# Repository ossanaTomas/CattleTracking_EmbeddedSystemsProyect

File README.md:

# Cattle Tracking System — Embedded Systems Project

## Table of Contents

- [Motivation](#motivation)
- [Overview](#overview)
- [Key Features](#key-features)
- [Repository Structure](#repository-structure)
- [Hardware Design](#hardware-design)
  - [Tracker Board (Collar Node)](#tracker-board-collar-node)
  - [Base Station Board](#base-station-board)
- [Firmware](#firmware)
  - [Tracker Firmware](#tracker-firmware-firmwarefirmware-tracker)
  - [Base Station Firmware](#base-station-firmware-firmwarefirmware-base-station)
- [Communication Protocol](#communication-protocol)
- [Dashboard Application](#dashboard-application-dashboard-app)
- [Technology Stack Summary](#technology-stack-summary)
- [Academic Context](#academic-context)
- [Author](#author)

---

## Motivation

My father is a farmer. Every single day he drives out to the field to walk the land, check on the animals, make sure they are healthy and in the right paddock. It is a time-consuming routine that depends entirely on being physically present.

That got me thinking: what if I could apply my knowledge as an engineering student to make his daily work easier? With a satellite tracking system he could simply pull out his phone, check an app, and know the status of every animal in real time — without leaving the house.

That question became this project. For the *Programación de Sistemas Embebidos* course I decided to build a **low-power, long-range embedded solution** that tackles exactly that problem. The result is a working prototype: custom PCBs, bare-metal firmware, a LoRa radio link, and a web dashboard, all built from scratch.

The system is still a prototype and has room to grow in several areas, but it is **fully functional** — and with a reasonable amount of additional development it could be deployed in a real field environment without any fundamental obstacles.

---

## Overview

An end-to-end **IoT solution for GPS-based livestock tracking** built entirely from scratch — custom PCBs, embedded firmware, and a web dashboard included.

The goal was to design a **low-power, long-range** monitoring system that can be attached to cattle collars. Each collar (tracker node) periodically collects GPS coordinates and body temperature, and transmits this data wirelessly to a fixed base station using **LoRa radio modules**. The base station forwards all received data to a PC, where a web application stores and visualizes it in real time.

```
┌─────────────────────────────────────────────────────────────────┐
│                         FIELD                                   │
│                                                                 │
│  ┌──────────────┐       LoRa        ┌──────────────────────┐   │
│  │   Tracker    │ ────────────────► │    Base Station      │   │
│  │  (Collar)    │ ◄──────── ACK/CFG │  (Fixed / Fencepost) │   │
│  │              │                   │                      │   │
│  │ STM32F103    │                   │ STM32F103            │   │
│  │ GPS (u-blox) │                   │ USB CDC              │   │
│  │ DS18B20 Temp │                   └──────────┬───────────┘   │
│  │ SX127x LoRa  │                              │               │
│  └──────────────┘                              │ USB Serial    │
│                                                │               │
└────────────────────────────────────────────────┼───────────────┘
                                                 │
                                    ┌────────────▼──────────────┐
                                    │     Dashboard App (PC)    │
                                    │   FastAPI + SQLite + Web  │
                                    └───────────────────────────┘
```

---

## Key Features

- **GPS tracking** — latitude, longitude, satellite count and heading, with 0.0001° precision
- **Temperature monitoring** — DS18B20 sensor with 0.001 °C resolution
- **Battery voltage monitoring** — reported in millivolts
- **LoRa radio link** — long-range, low-power wireless communication (SX127x modules)
- **Two operating modes** — Continuous (every 30 s) and Low-Power (configurable interval with GPS pre-warming)
- **Reliable delivery (Stop-and-Wait ARQ)** — every DATA frame is acknowledged; unacknowledged frames are retried
- **Remote reconfiguration** — the base station can push configuration changes (mode, interval, GPS timers) via piggybacked ACK frames
- **Persistent configuration** — node settings survive power cycles (stored in Flash)
- **CRC16-CCITT integrity checks** — every frame is verified on both ends
- **Comprehensive error reporting** — 16-bit error mask covers GPS fix failures, sensor errors, battery alerts, and radio issues
- **Web dashboard** — real-time visualization of all received telemetry; debug view with raw frame inspection

---

## Repository Structure

```
EmbeddedSystemProyect/
├── firmware/
│   ├── firmware-tracker/          # STM32 firmware for the collar node
│   │   ├── Core/
│   │   │   ├── Inc/               # Header files
│   │   │   └── Src/               # C source files
│   │   ├── Drivers/               # STM32 HAL + CMSIS
│   │   └── EmbeddedSystemProyect.ioc
│   └── firmware-base-station/     # STM32 firmware for the base station
│       ├── Core/
│       │   ├── Inc/
│       │   └── Src/
│       ├── Drivers/
│       ├── Middlewares/           # USB Device stack (CDC)
│       └── Base_station.ioc
├── hardware/
│   ├── kicad/
│   │   ├── tracker-board/         # KiCad schematic + PCB for the collar
│   │   └── base-station-board/    # KiCad schematic + PCB for the base station
│   └── images/
│       ├── tracker-boad/          # Schematics, renders, and photos — tracker
│       └── base-station-board/    # Schematics, renders, and photos — base station
└── dashboard-app/                 # Python FastAPI web application
    ├── app/
    │   ├── api/                   # REST endpoints
    │   ├── db/                    # SQLAlchemy models + SQLite session
    │   ├── proto/                 # Frame parser + CRC16
    │   ├── serial/                # Serial port reader (USB CDC)
    │   └── web/                   # Jinja2 templates (dashboard, debug, mode)
    └── requirements.txt
```

---

## Hardware Design

Both boards were designed from scratch in **KiCad**, manufactured, hand-assembled, and tested.

### Tracker Board (Collar Node)

The tracker is a compact, battery-powered board designed to be mounted on a livestock collar. It integrates the microcontroller, LoRa module footprint, GPS connector, temperature sensor interface, and power management in a single PCB.

**Schematic**

**PCB Layout**

**3D Renders**

| Front | Back |
|-------|------|
|  |  |

**Fabrication & Assembly**

**Mounted on Collar**

---

### Base Station Board

The base station is a fixed-installation board. It receives LoRa frames from all trackers in range and forwards the raw data to a PC over USB (CDC virtual serial port).

**Schematic**

**PCB Layout**

**3D Renders**

**Fabrication & Result**

---

## Firmware

Both firmware projects target the **STM32F103C8T6** (ARM Cortex-M3, 64 KB Flash, 20 KB RAM) and were developed using **STM32CubeIDE**. 

### Tracker Firmware (`firmware/firmware-tracker`)

The tracker firmware follows a clean layered architecture:

```
┌─────────────────────────────────────────┐
│          Application Layer              │  node.c — NodeSimple_Task()
│  (mode management, data collection,     │  node_cfg.c — Flash persistence
│   TX scheduling, RX window)             │
├─────────────────────────────────────────┤
│           Service Layer                 │  gps.c — NMEA / UBX parser
│  (sensor acquisition, GPS management,  │  service_temp.c — DS18B20 service
│   temperature, battery)                 │
├─────────────────────────────────────────┤
│          Protocol Layer                 │  frame.c — pack/unpack frames
│  (framing, CRC16, ARQ link layer)       │  crc16_ccitt.c
│                                         │  node_link.c — Stop-and-Wait ARQ
├─────────────────────────────────────────┤
│       Hardware Abstraction Layer        │  LoRa.c — SX127x SPI driver
│  (LoRa radio, OneWire, UART, SPI, GPIO) │  ds18b20.c + onewire_uart.c
│                                         │  STM32 HAL (SPI1, USART1/2, GPIO)
└─────────────────────────────────────────┘
```

#### Peripheral Mapping

| Peripheral | Pins | Purpose |
|-----------|------|---------|
| SPI1 | PA5 / PA6 / PA7 | LoRa SX127x data bus (SCK / MISO / MOSI) |
| GPIO | PB0 / PB1 / PB10 | LoRa NSS (chip-select) / RST / DIO0 (IRQ) |
| USART1 | PA9 / PA10 | GPS UART @ 9600 baud (NMEA + UBX) |
| GPIO | PB11 | GPS power enable |
| USART2 | PA2 (half-duplex) | OneWire bus for DS18B20 @ 115200 baud |
| GPIO | PC13 | Status LED |
| SWD | PA13 / PA14 | Programming interface |

#### Operating Modes

**Continuous Mode (`NODE_MODE_CONTINUOUS`)**
Transmits a DATA frame every 30 seconds with the GPS running continuously. Prioritizes update frequency over power consumption — suitable for short-duration operations or testing.

**Low-Power Mode (`NODE_MODE_LOW_POWER`)**
Designed for multi-day battery life. The GPS is kept off between transmissions. Before each scheduled TX, the GPS is powered on for a configurable pre-warm period (`gps_prewarm_s`) to start acquiring satellites. An additional wait (`gps_extra_wait_s`) is allowed to obtain a valid fix. After transmission, the GPS is powered down again.

Both modes and their timing parameters are configurable and persist across reboots in **Flash memory** (last 1 KB page at address `0x0800F800`).

#### Reliable Delivery (Stop-and-Wait ARQ)

After each DATA frame is transmitted, the node opens a **receive window** waiting for an ACK from the base station. If no ACK is received within the timeout, the frame is retried up to `n_retries` times. The ACK frame can optionally carry a `CFG` payload, allowing the base station to push updated configuration to the node without a separate control channel.

#### Initialization Sequence

```
HAL_Init() → SystemClock_Config()
  → MX_GPIO_Init()
  → MX_USART1_UART_Init()  (GPS @ 9600 baud)
  → MX_USART2_UART_Init()  (OneWire / DS18B20 @ 115200 baud)
  → MX_SPI1_Init()         (LoRa @ 8 Mbit/s)
  → GPS_Init()
  → TempService_Init(&huart2, DS18B20_RES_10BIT)
  → LoRa_init()            (retried up to 50 times)
  → NodeSimple_Init(lora, node_id=1, net_id=0x27)
  → while(1) NodeSimple_Task()
```

---

### Base Station Firmware (`firmware/firmware-base-station`)

The base station is simpler by design. Its responsibilities are:

1. Continuously listen on the LoRa channel for incoming DATA frames
2. Send an ACK frame back to the transmitting node (optionally with a CFG payload)
3. Forward received frames to the PC over **USB CDC** (virtual serial port)
4. Accept commands from the PC (`pc_cmd.c`) to push configuration changes to specific nodes

It exposes a USB CDC virtual COM port to the host PC, over which raw received frames (prefixed with RSSI) are streamed. The dashboard app reads this serial stream.

---

## Communication Protocol

All LoRa transmissions use a custom binary framing protocol with CRC integrity verification.

### Frame Structure

```
 ┌──────────────────────────┬────────────────────┬───────────────┐
 │       HEADER (8 bytes)   │  PAYLOAD (variable) │  CRC16 (2 B)  │
 └──────────────────────────┴────────────────────┴───────────────┘

Header fields:
  [0] VER    — Protocol version (0x01)
  [1] NET    — Network ID (0x27 by default)
  [2] TYPE   — Message type
  [3] SRC    — Source node address
  [4] DST    — Destination address (0xFF = broadcast)
  [5] SEQ    — Sequence number (0–255, wraps around)
  [6] FLAGS  — Validity bits (GPS_VALID | TEMP_VALID | BATT_VALID)
  [7] PLEN   — Payload length in bytes
```

### Message Types

| Type | Code | Direction | Description |
|------|------|-----------|-------------|
| DATA | `0x10` | Tracker → Base | Sensor telemetry payload |
| ERR  | `0x11` | Tracker → Base | Error notification with text |
| ACK  | `0x30` | Base → Tracker | Acknowledgment (may carry CFG) |
| CFG  | `0x20` | Base → Tracker | Remote configuration update |

### DATA Payload (27 bytes)

```c
typedef struct {
    uint32_t t_ms;            // Node uptime in milliseconds
    uint32_t utc_raw_x1e3;    // UTC time from GPS (x1000)
    int32_t  lat_raw_x1e4;    // Latitude  ddmm.mmmm x 10000 (negative = S)
    int32_t  lon_raw_x1e4;    // Longitude dddmm.mmmm x 10000 (negative = W)
    uint8_t  sats;            // Number of satellites in view
    uint16_t course_cdeg;     // Heading in centidegrees (degrees x 100)
    int32_t  temp_mC;         // Temperature in milli-Celsius
    uint16_t batt_mV;         // Battery voltage in millivolts
    uint16_t err_mask;        // 16-bit error flags
} proto_data_t;
```

### Error Mask Bits

| Bit | Meaning |
|-----|---------|
| 0 | GPS no fix |
| 1 | GPS parse error |
| 2 | GPS configuration error |
| 3 | Temperature sensor read failure |
| 4 | Temperature sensor not detected |
| 5 | Battery voltage critical |
| 6 | LoRa TX failure |
| 7 | ACK timeout (max retries exceeded) |
| 8 | CRC verification failure |

### CFG Payload (6 bytes)

The base station can remotely reconfigure any tracker by piggybacking a CFG payload onto the ACK response:

```c
typedef struct {
    uint8_t  cfg_seq;        // Sequence number (idempotent updates)
    uint8_t  mode;           // 0 = CONTINUOUS, 1 = LOW_POWER
    uint16_t interval_s;     // TX interval in seconds (Low-Power mode)
    uint8_t  gps_prewarm_s;  // Seconds to power GPS before TX
    uint8_t  gps_extra_s;    // Extra seconds to wait for GPS fix
} proto_cfg_t;
```

---

## Dashboard Application (`dashboard-app`)

A Python web application that receives telemetry from the base station and exposes it through a browser-based interface.

### Architecture

```
USB Serial (base station)
        │
        ▼
  SerialManager        ← background thread, reads raw frames
        │
        ▼
  Frame Parser         ← unpack header + payload, verify CRC16
        │
        ▼
  SQLite Database      ← stores Node and Frame records (SQLAlchemy)
        │
        ├──► REST API  (/api/...)   ← JSON endpoints
        └──► Web UI    (/dashboard, /debug, /mode)
```

### Components

| Module | Role |
|--------|------|
| `serial/serial_manager.py` | Reads raw bytes from USB CDC serial port in a background thread |
| `proto/frame.py` | Unpacks binary frames, parses DATA payload, converts raw coordinates to decimal degrees |
| `proto/crc16.py` | CRC16-CCITT verification |
| `db/models.py` | `Node` and `Frame` SQLAlchemy ORM models |
| `api/routes.py` | REST endpoints exposing stored telemetry as JSON |
| `web/templates/dashboard.html` | Main live telemetry dashboard |
| `web/templates/debug.html` | Raw frame inspection view |
| `web/templates/mode.html` | Push configuration changes to nodes |

### Frame Deduplication

The tracker can transmit the same frame twice as a redundancy measure. The dashboard app silently deduplicates frames with the same `(node_id, seq)` arriving within a 5-second window before storing them in the database. It also tracks sequence number gaps to detect lost packets.

### Tech Stack

| Library | Version | Purpose |
|---------|---------|---------|
| FastAPI | 0.115.0 | Web framework + REST API |
| Uvicorn | 0.30.6 | ASGI server |
| SQLAlchemy | 2.0.32 | ORM + SQLite session management |
| Pydantic | 2.8.2 | Data validation and schemas |
| pyserial | 3.5 | USB CDC serial communication |
| Jinja2 | 3.1.4 | HTML templating |

### Running the Dashboard

```bash
cd dashboard-app
pip install -r requirements.txt
uvicorn app.main:app --reload
```

Then open `http://localhost:8000/dashboard` in a browser.

The app auto-detects the base station's COM port. If multiple serial ports are available, it can be specified via the `SERIAL_PORT` environment variable:

```bash
SERIAL_PORT=COM3 uvicorn app.main:app --reload
```

---

## Technology Stack Summary

| Layer | Technology |
|-------|-----------|
| Microcontroller | STM32F103C8T6 (ARM Cortex-M3 @ 16 MHz, 64 KB Flash, 20 KB RAM) |
| IDE / Toolchain | STM32CubeIDE + GNU ARM Embedded (arm-none-eabi-gcc) |
| HAL | STM32 HAL (SPI, UART, GPIO, USB Device) |
| Radio | LoRa SX127x (SPI @ 8 Mbit/s) |
| GPS | u-blox NEO6Mv2  (NMEA + UBX, UART @ 9600 baud) |
| Temperature | DS18B20 via OneWire-over-UART (UART @ 115200 baud, half-duplex) |
| PCB Design | KiCad |
| Backend | Python 3, FastAPI, SQLAlchemy, SQLite |
| Frontend |(server-rendered HTML) |

---

## Academic Context

This project was developed as the final deliverable for the **Programación de Sistemas Embebidos** course at **Universidad Católica de Córdoba (UCC)**, Faculty of Engineering. The course focuses on bare-metal and HAL-based programming for ARM Cortex-M microcontrollers, primarily using ST boards (STM32 Blue Pill, STM32 Discovery).

The project was structured as two incremental deliveries:

- **Partial 1** — Initial hardware design and basic sensor + LoRa communication prototype
- **Partial 2** — Full system integration: reliable delivery, operating modes, configuration persistence, and dashboard application

The complete system was presented and demonstrated working as the final exam.

---

## Author

👨‍💻 **Tomás Ossana**

Computer Engineering student — Universidad Católica de Córdoba (UCC), Argentina.

This project was built for educational purposes and puts into practice fundamental concepts acquired throughout the course and the degree, spanning both software and hardware development. 

It was a challenging, integrative, and genuinely enjoyable project from start to finish. Every module integration came with its own set of obstacles, and solving them was just as satisfying as watching the complete system work end to end. I leaned and enjoy a lot during this subjet and that's the most important of all!! 

---
*Universidad Católica de Córdoba — Ingeniería en Computación — 2025*

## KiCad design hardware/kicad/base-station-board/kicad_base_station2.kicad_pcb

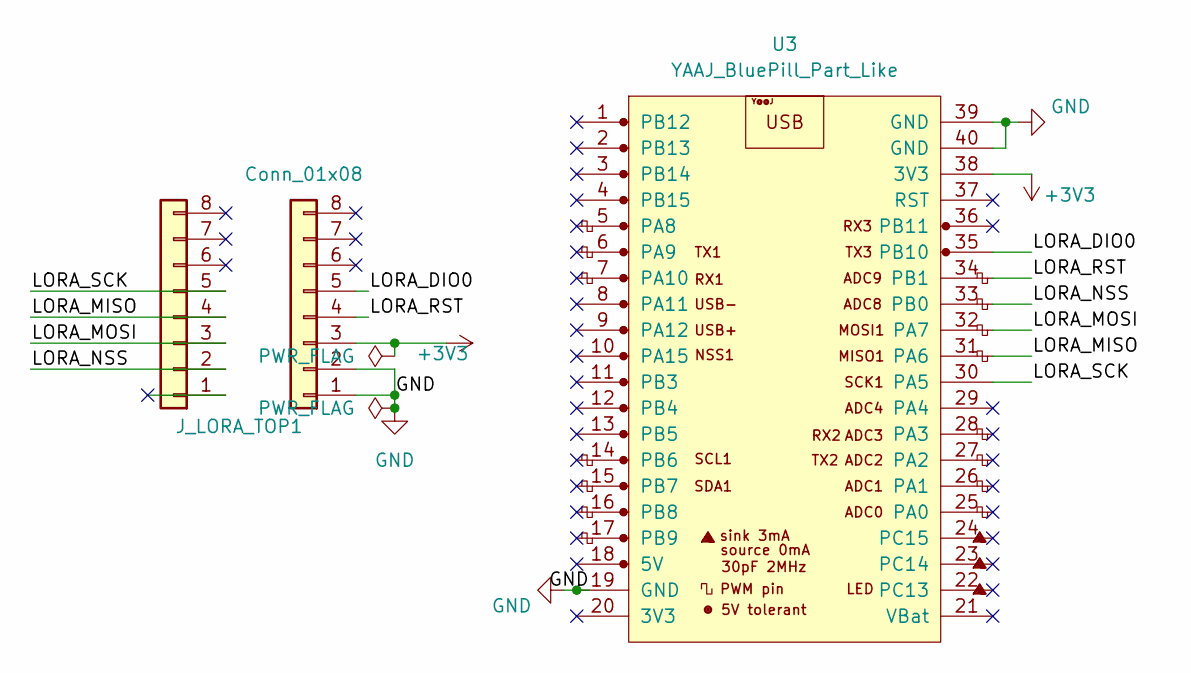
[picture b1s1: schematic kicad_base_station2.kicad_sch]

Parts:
J_LORA_BOT1: Conn_01x08; PinSocket_1x08_P2.54mm_Vertical
J_LORA_TOP1: Conn_01x08; PinSocket_1x08_P2.54mm_Vertical
U3: YAAJ_BluePill_Part_Like; YAAJ_BluePill_1

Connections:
+3V3: J_LORA_BOT1.3, U3.38 (3V3)
/LORA_DIO0: J_LORA_BOT1.5, U3.35 (PB10)
/LORA_MISO: J_LORA_TOP1.4, U3.31 (PA6)
/LORA_MOSI: J_LORA_TOP1.3, U3.32 (PA7)
/LORA_NSS: J_LORA_TOP1.2, U3.33 (PB0)
/LORA_RST: J_LORA_BOT1.4, U3.34 (PB1)
/LORA_SCK: J_LORA_TOP1.5, U3.30 (PA5)
GND: J_LORA_BOT1.1, J_LORA_BOT1.2, U3.19 (GND), U3.39 (GND), U3.40 (GND)

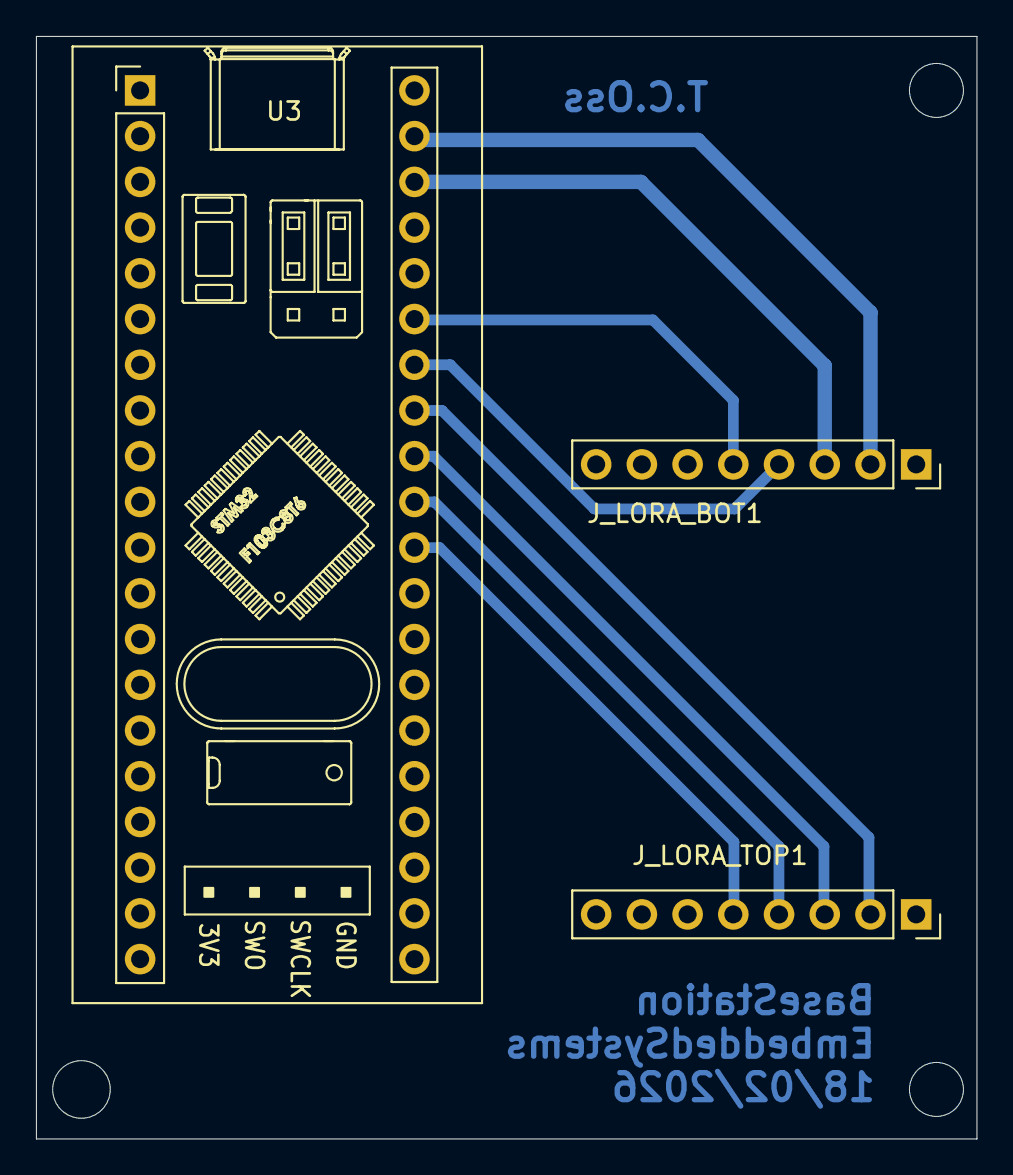
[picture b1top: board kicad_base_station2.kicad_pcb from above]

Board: 2 copper layers, 52.2 x 61.2 mm, 3 parts (0 on the bottom side), 8 nets.

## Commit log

2026-02-10 feat(gps): support GGA and RMC parsing; UBX configurations messages; filter unused NMEA sentences
2026-02-11 feat(gps): store UBX configuration persistently; restore defaults; add checksum + redundancy on UBX messages
2026-02-12 feat(Termometer): library for reading temperature
2026-02-13 refactor(thermometer): update reading temperature method;
2026-02-14 feat(termometer):add termperature reading average method
2026-02-14 feat(LoRa): add LoRa library
2026-02-15 Refactor(LoRa): Change init LoRa method; SPI integration
2026-02-17 Some minor changes
2026-02-19 feat(frame):add frame logic and post marge LoRa
2026-02-22 Feat: Add turn On-Off GPS; Add UTC time to frame
2026-03-11 refactor(frame): change protocol tranmission logic
2026-03-11 Reorganize repository structure for tracker and base station firmware
2026-03-11 Add dashboard application
2026-03-11 Add kicad base-station board files
2026-03-11 Add kicad tracker board files
2026-03-11 Add tracker and base station images; fix some filesnames
2026-03-11 Reorganize firmware directories under firmware folder
2026-03-31 Add complete Readme
2026-03-31 docs: finish project README
